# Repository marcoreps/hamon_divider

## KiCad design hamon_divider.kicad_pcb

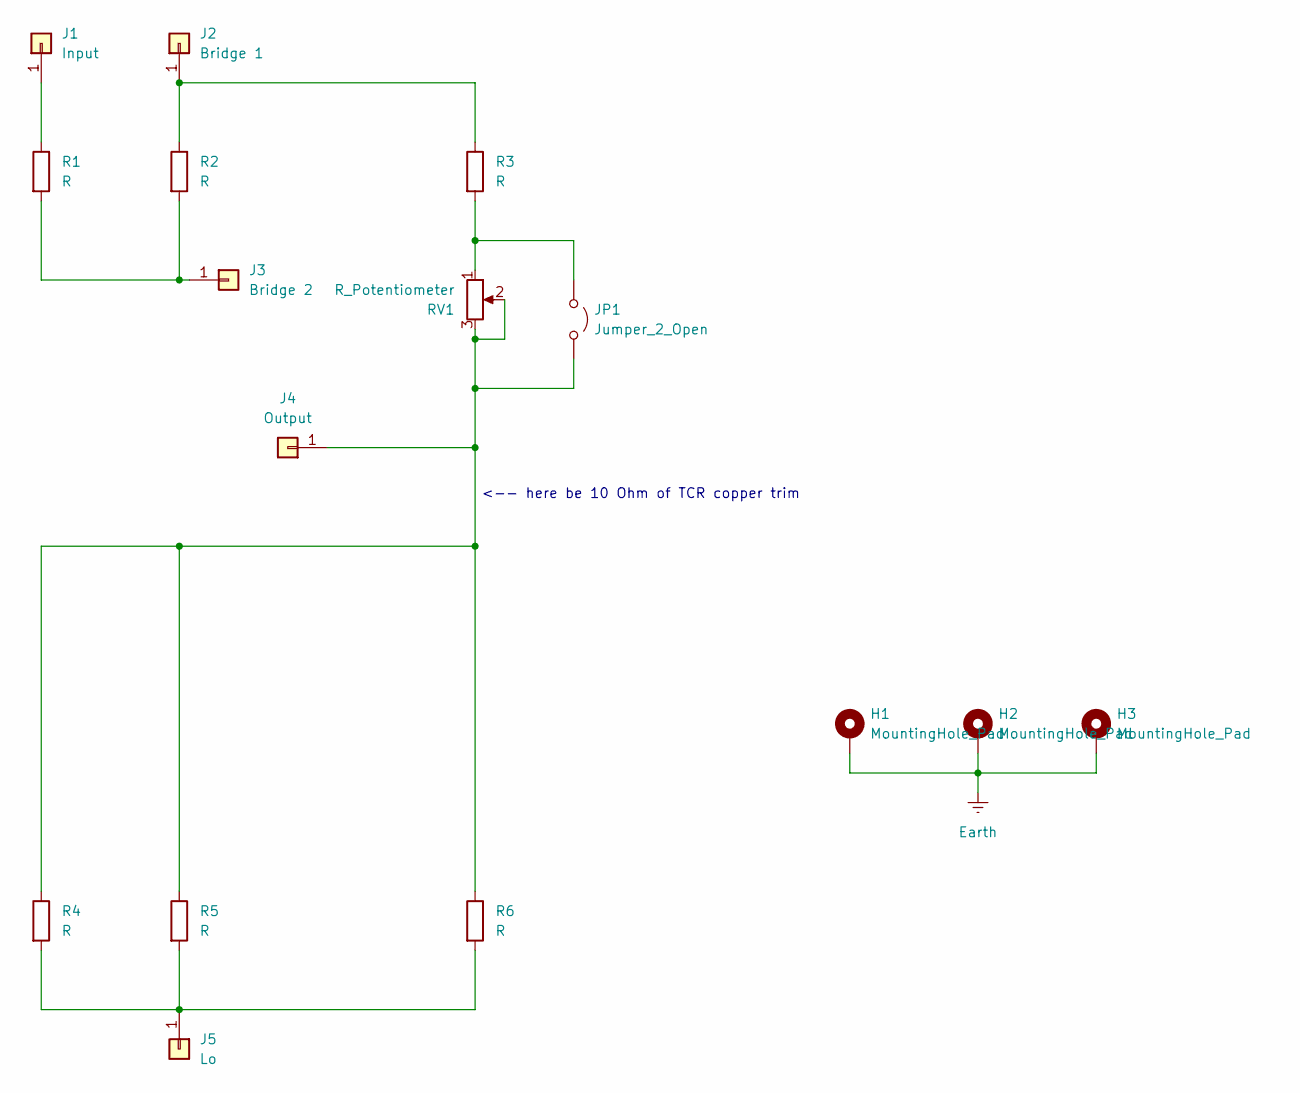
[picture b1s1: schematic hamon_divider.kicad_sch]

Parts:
H1, H2, H3: MountingHole_Pad; MountingHole_3.2mm_M3_DIN965_Pad
J1: Input; SolderWire-0.5sqmm_1x01_D0.9mm_OD2.1mm
J2: Bridge 1; SolderWire-0.5sqmm_1x01_D0.9mm_OD2.1mm
J3: Bridge 2; SolderWire-0.5sqmm_1x01_D0.9mm_OD2.1mm
J4: Output; SolderWire-0.5sqmm_1x01_D0.9mm_OD2.1mm
J5: Lo; SolderWire-0.5sqmm_1x01_D0.9mm_OD2.1mm
JP1: Jumper_2_Open; SolderJumper-2_P1.3mm_Open_Pad1.0x1.5mm
R1, R2, R3, R4, R5, R6: R; Crystal_HC52-U_Vertical
RV1: R_Potentiometer; Potentiometer_ACP_CA9-H2,5_Horizontal

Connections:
Earth: H1.1, H2.1, H3.1
unnamed: J1.1, R1.1
unnamed: J2.1, R2.1, R3.1
unnamed: J3.1, R1.2, R2.2
unnamed: J4.1, JP1.2 (B), R4.1, R5.1, R6.1, RV1.2, RV1.3
unnamed: J5.1, R4.2, R5.2, R6.2
unnamed: JP1.1 (A), R3.2, RV1.1

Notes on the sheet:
<-- here be 10 Ohm of TCR copper trim

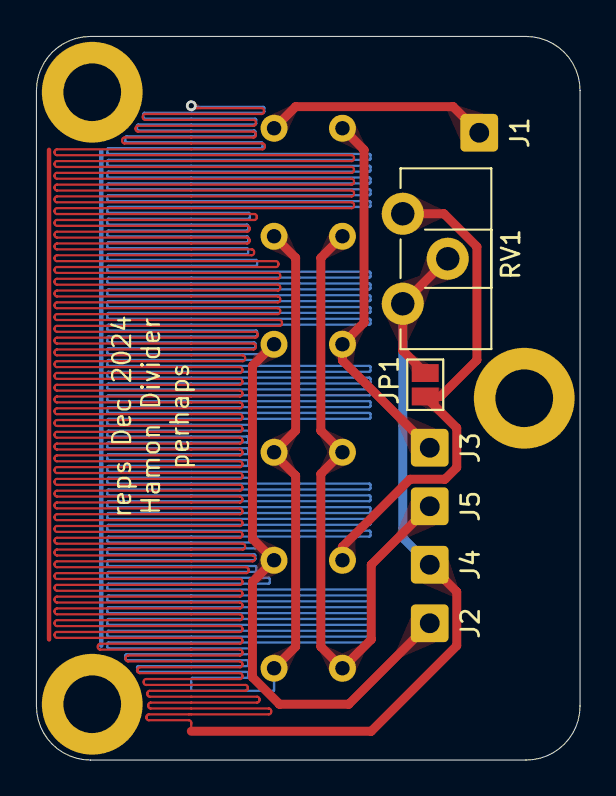
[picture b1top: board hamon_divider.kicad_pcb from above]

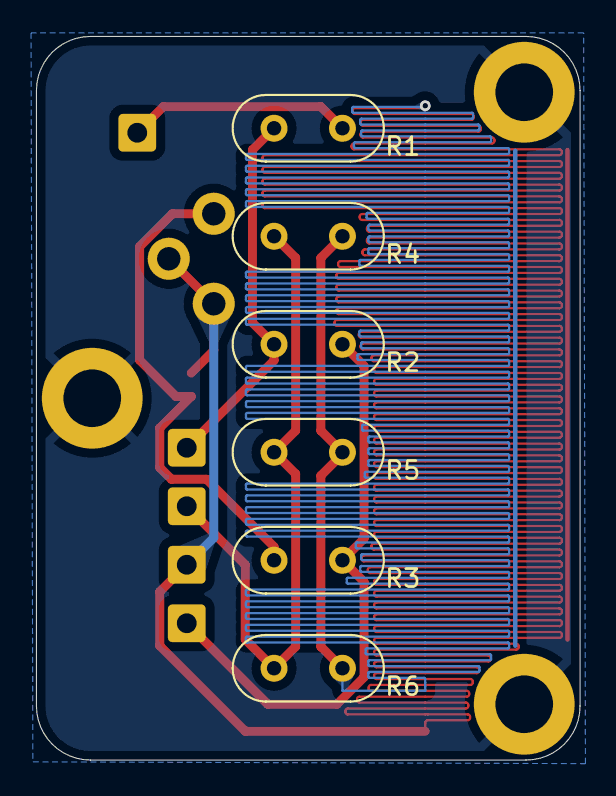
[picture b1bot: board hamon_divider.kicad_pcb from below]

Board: 4 copper layers, 30.2 x 40.2 mm, 16 parts (6 on the bottom side), 7 nets.

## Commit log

2025-01-31 asdf
